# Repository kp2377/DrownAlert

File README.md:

## Drown Alert

This is the final Project submission for RTES course work.

### Things designed :-

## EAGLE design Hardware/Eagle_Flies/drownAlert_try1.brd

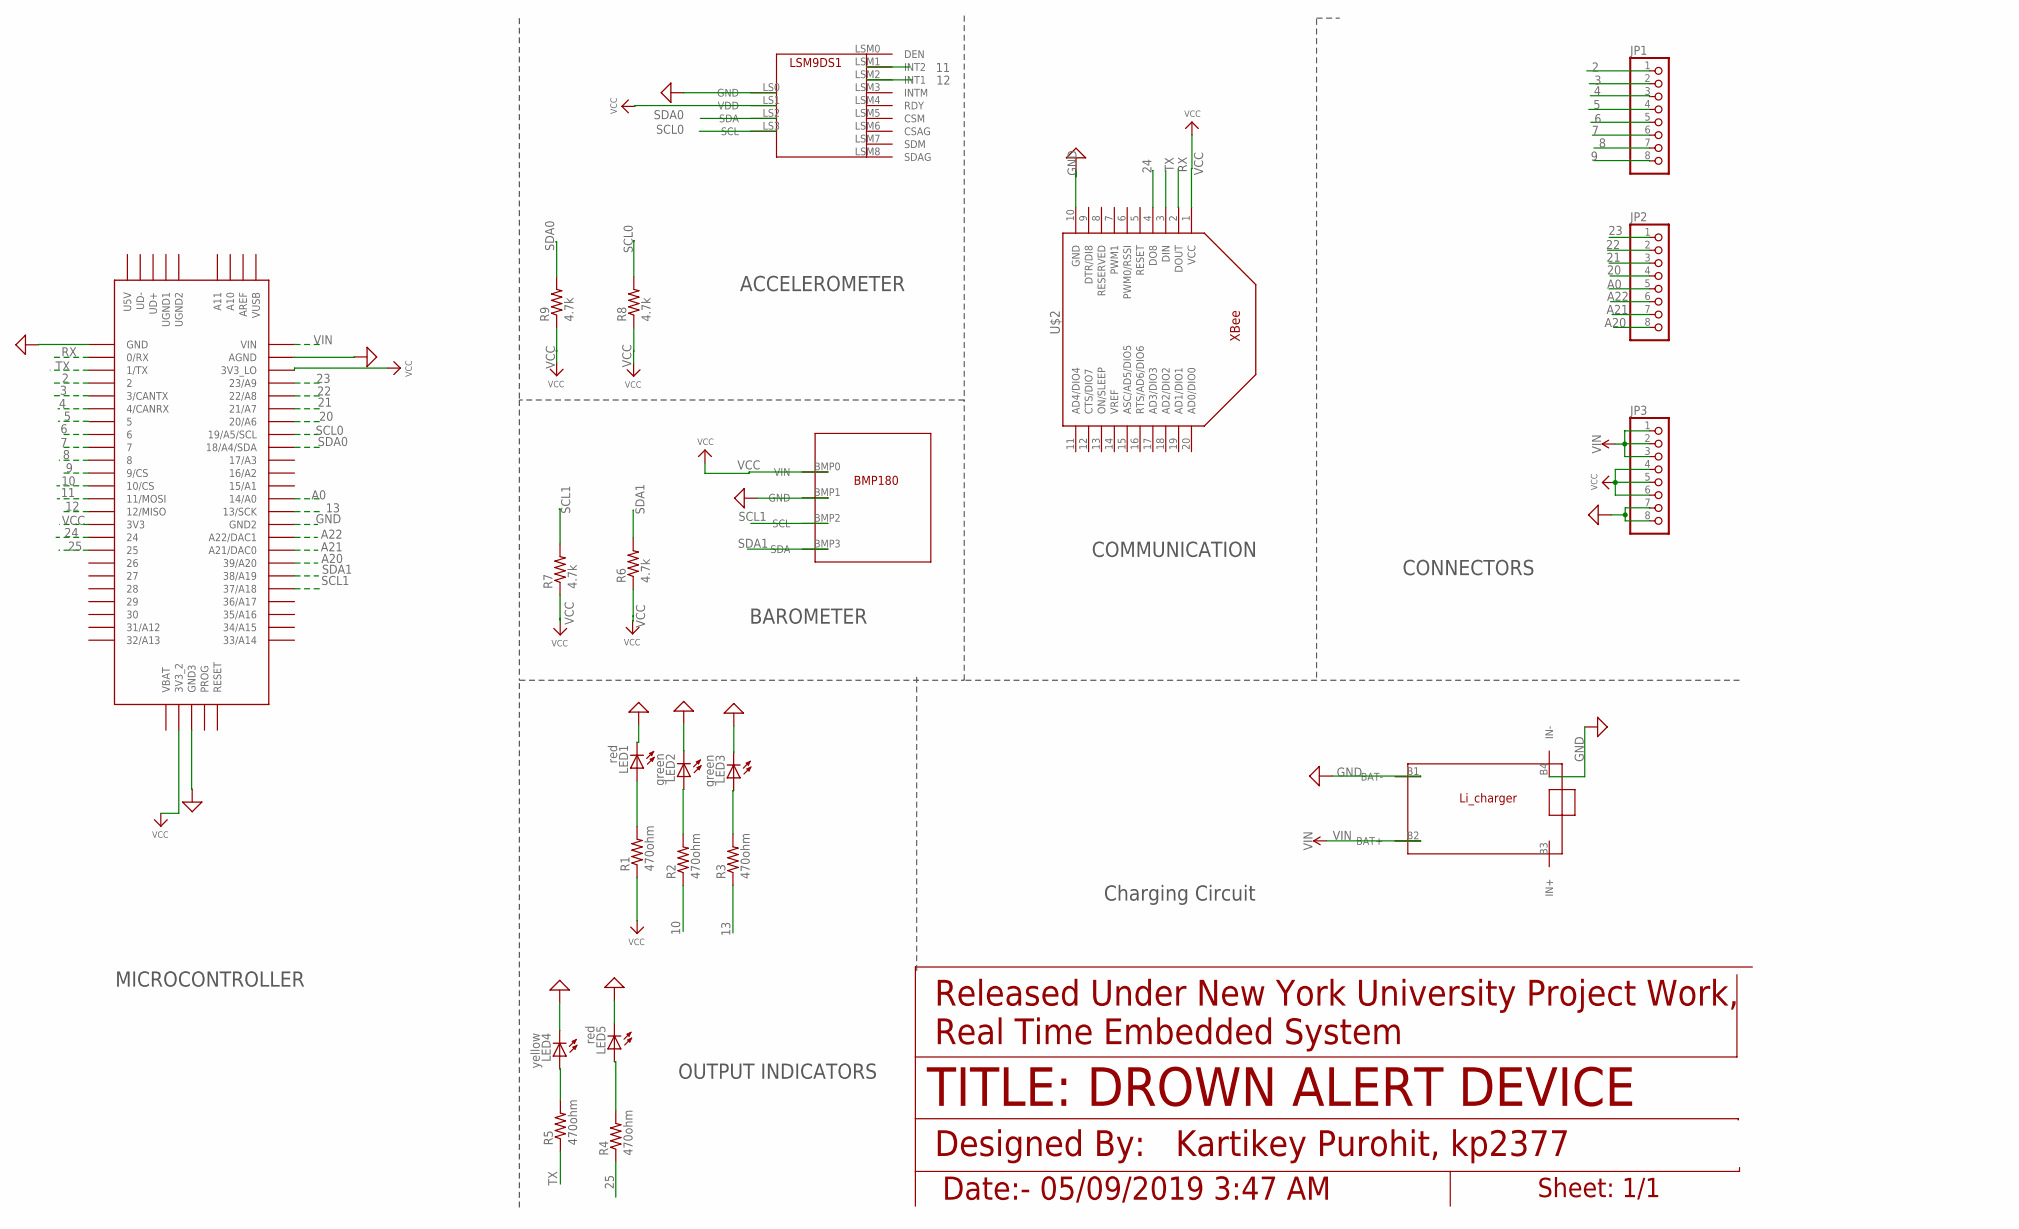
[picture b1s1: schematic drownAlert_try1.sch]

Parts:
JP1, JP2, JP3: PINHD-1X8-3.5MM; 1X08-3.5MM
LED1, LED5: red; CHIPLED_1206
LED2, LED3: green; CHIPLED_1206
LED4: yellow; CHIPLED_1206
R1, R2, R3, R4, R5: 470ohm; R1206
R6, R7, R8, R9: 4.7k; R1206
U$1: TEENSY_3.5/3.6
U$2: XBEE
U$3: KKP_BATTERY_CHARGER; KKP_CUSTOM_BATTERY_CHARGER
U$5: KKP_BMP180; KKP_CUSTOM_BMP180
U$6: KKP_LSM; KKP_CUSTOM_LSM9D-S1_FOOTPRINT

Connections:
2: JP1.1, U$1.2
3: JP1.2, U$1.3/CANTX
4: JP1.3, U$1.4/CANRX
5: JP1.4, U$1.5
6: JP1.5, U$1.6
7: JP1.6, U$1.7
8: JP1.7, U$1.8
9: JP1.8, U$1.9/CS
10: R2.1, U$1.10/CS
11: U$1.11/MOSI, U$6.LSM1 (INT2)
12: U$1.12/MISO, U$6.LSM2 (INT1)
13: R3.1, U$1.13/SCK
20: JP2.4, U$1.20/A6
21: JP2.3, U$1.21/A7
22: JP2.2, U$1.22/A8
23: JP2.1, U$1.23/A9
24: U$1.24, U$2.4 (DO8)
25: R4.1, U$1.25
A0: JP2.5, U$1.14/A0
A20: JP2.8, U$1.39/A20
A21: JP2.7, U$1.21/DAC0 (A21/DAC0)
A22: JP2.6, U$1.A22/DAC1
GND: JP3.7, JP3.8, LED1.C, LED2.C, LED3.C, LED4.C, LED5.C, U$1.AGND, U$1.GND, U$1.GND2, U$1.GND3, U$2.10 (GND), U$3.B1 (BAT-), U$3.B4 (IN-), U$5.BMP1 (GND), U$6.LS0 (GND)
unnamed: LED1.A, R1.2
unnamed: LED2.A, R2.2
unnamed: LED3.A, R3.2
unnamed: LED4.A, R5.2
unnamed: LED5.A, R4.2
RX: U$1.0/RX, U$2.2 (DOUT)
SCL0: R8.2, U$1.19/A5/SCL, U$6.LS3 (SCL)
SCL1: R7.2, U$1.37/A18, U$5.BMP2 (SCL)
SDA0: R9.2, U$1.18/A4/SDA, U$6.LS2 (SDA)
SDA1: R6.2, U$1.38/A19, U$5.BMP3 (SDA)
TX: R5.1, U$1.1/TX, U$2.3 (DIN)
VCC: JP3.4, JP3.5, JP3.6, R1.1, R6.1, R7.1, R8.1, R9.1, U$1.3V3, U$1.3V3_2, U$1.3V3_LO, U$2.1 (VCC), U$5.BMP0 (VIN), U$6.LS1 (VDD)
VIN: JP3.1, JP3.2, JP3.3, U$1.VIN, U$3.B2 (BAT+)

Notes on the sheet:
Released Under New York University Project Work, Real Time Embedded System
TITLE: DROWN ALERT DEVICE
Designed By: Kartikey Purohit, kp2377
Sheet: 1/1
Date:- 05/09/2019 3:47 AM
COMMUNICATION
CONNECTORS
Charging Circuit
OUTPUT INDICATORS
MICROCONTROLLER
ACCELEROMETER
BAROMETER

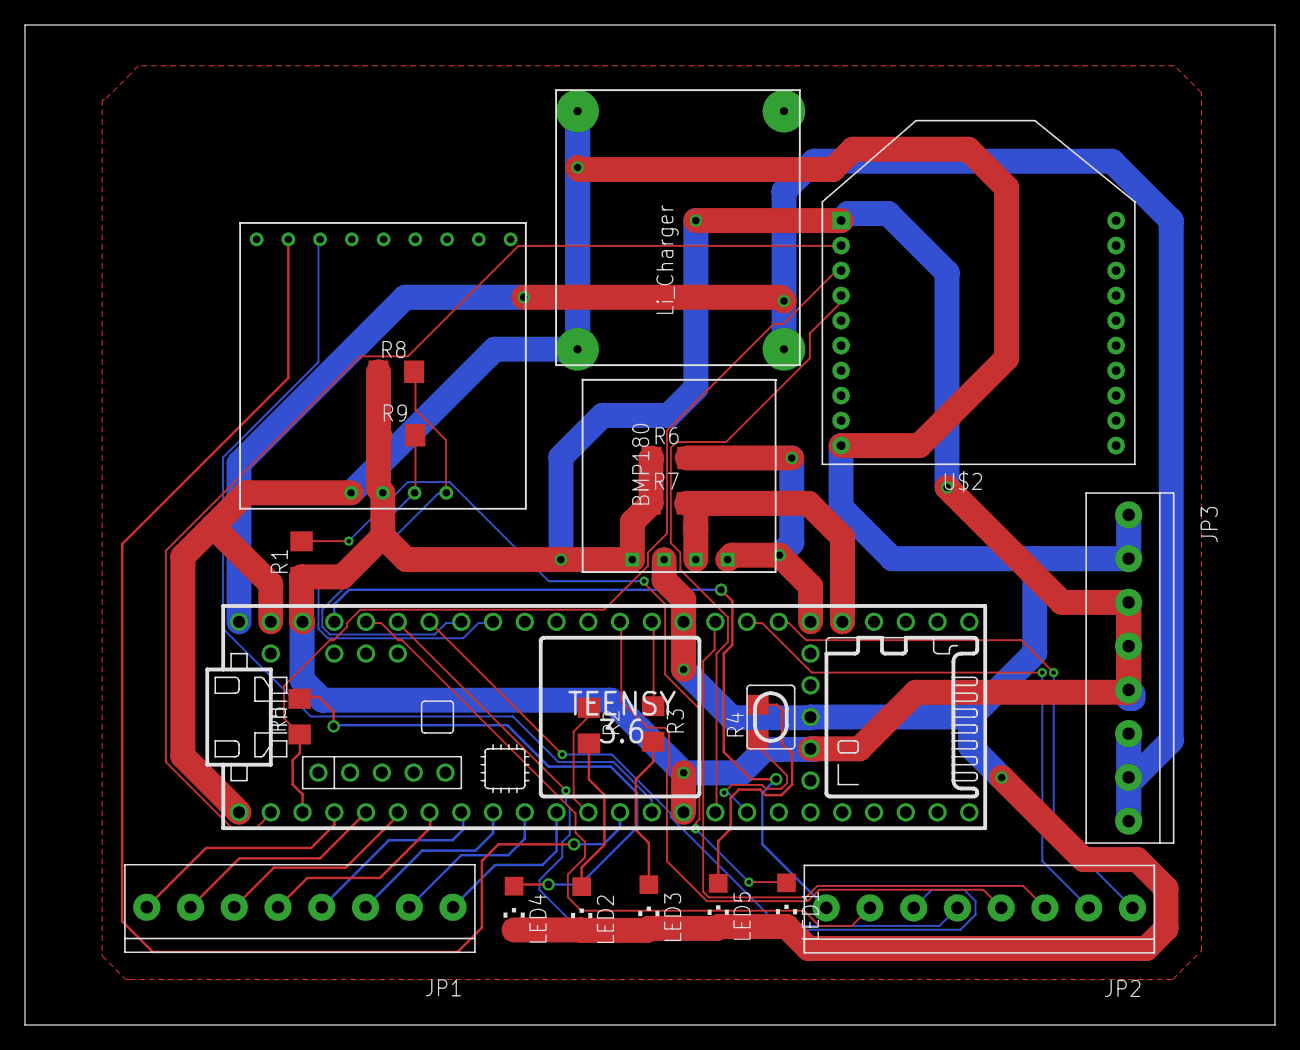
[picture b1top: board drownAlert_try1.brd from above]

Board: 2 copper layers, 100.0 x 80.0 mm, 22 parts (0 on the bottom side), 36 nets.

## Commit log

2019-04-25 first commit
    example directly copied!!
2019-05-02 accelerometer threshold
    The first commit that include acceleration threshold being set completely
2019-05-13 Second Commit
    Here, the barometer added. The function of gyro and accelerometer modifies.
2019-05-13 Third Commit
    Added all the Eagle Hardware files and 3D Model
2019-05-13 Final timer integrated
    in The code millis() has been added
2019-05-16 last comiit for the project
    its working
2019-07-07 Set theme jekyll-theme-cayman

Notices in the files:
parts and their libraries:
SparkFun-PowerSymbols: Licensing: Creative Commons ShareAlike 4.0 International - https://creativecommons.org/licenses/by-sa/4.0
